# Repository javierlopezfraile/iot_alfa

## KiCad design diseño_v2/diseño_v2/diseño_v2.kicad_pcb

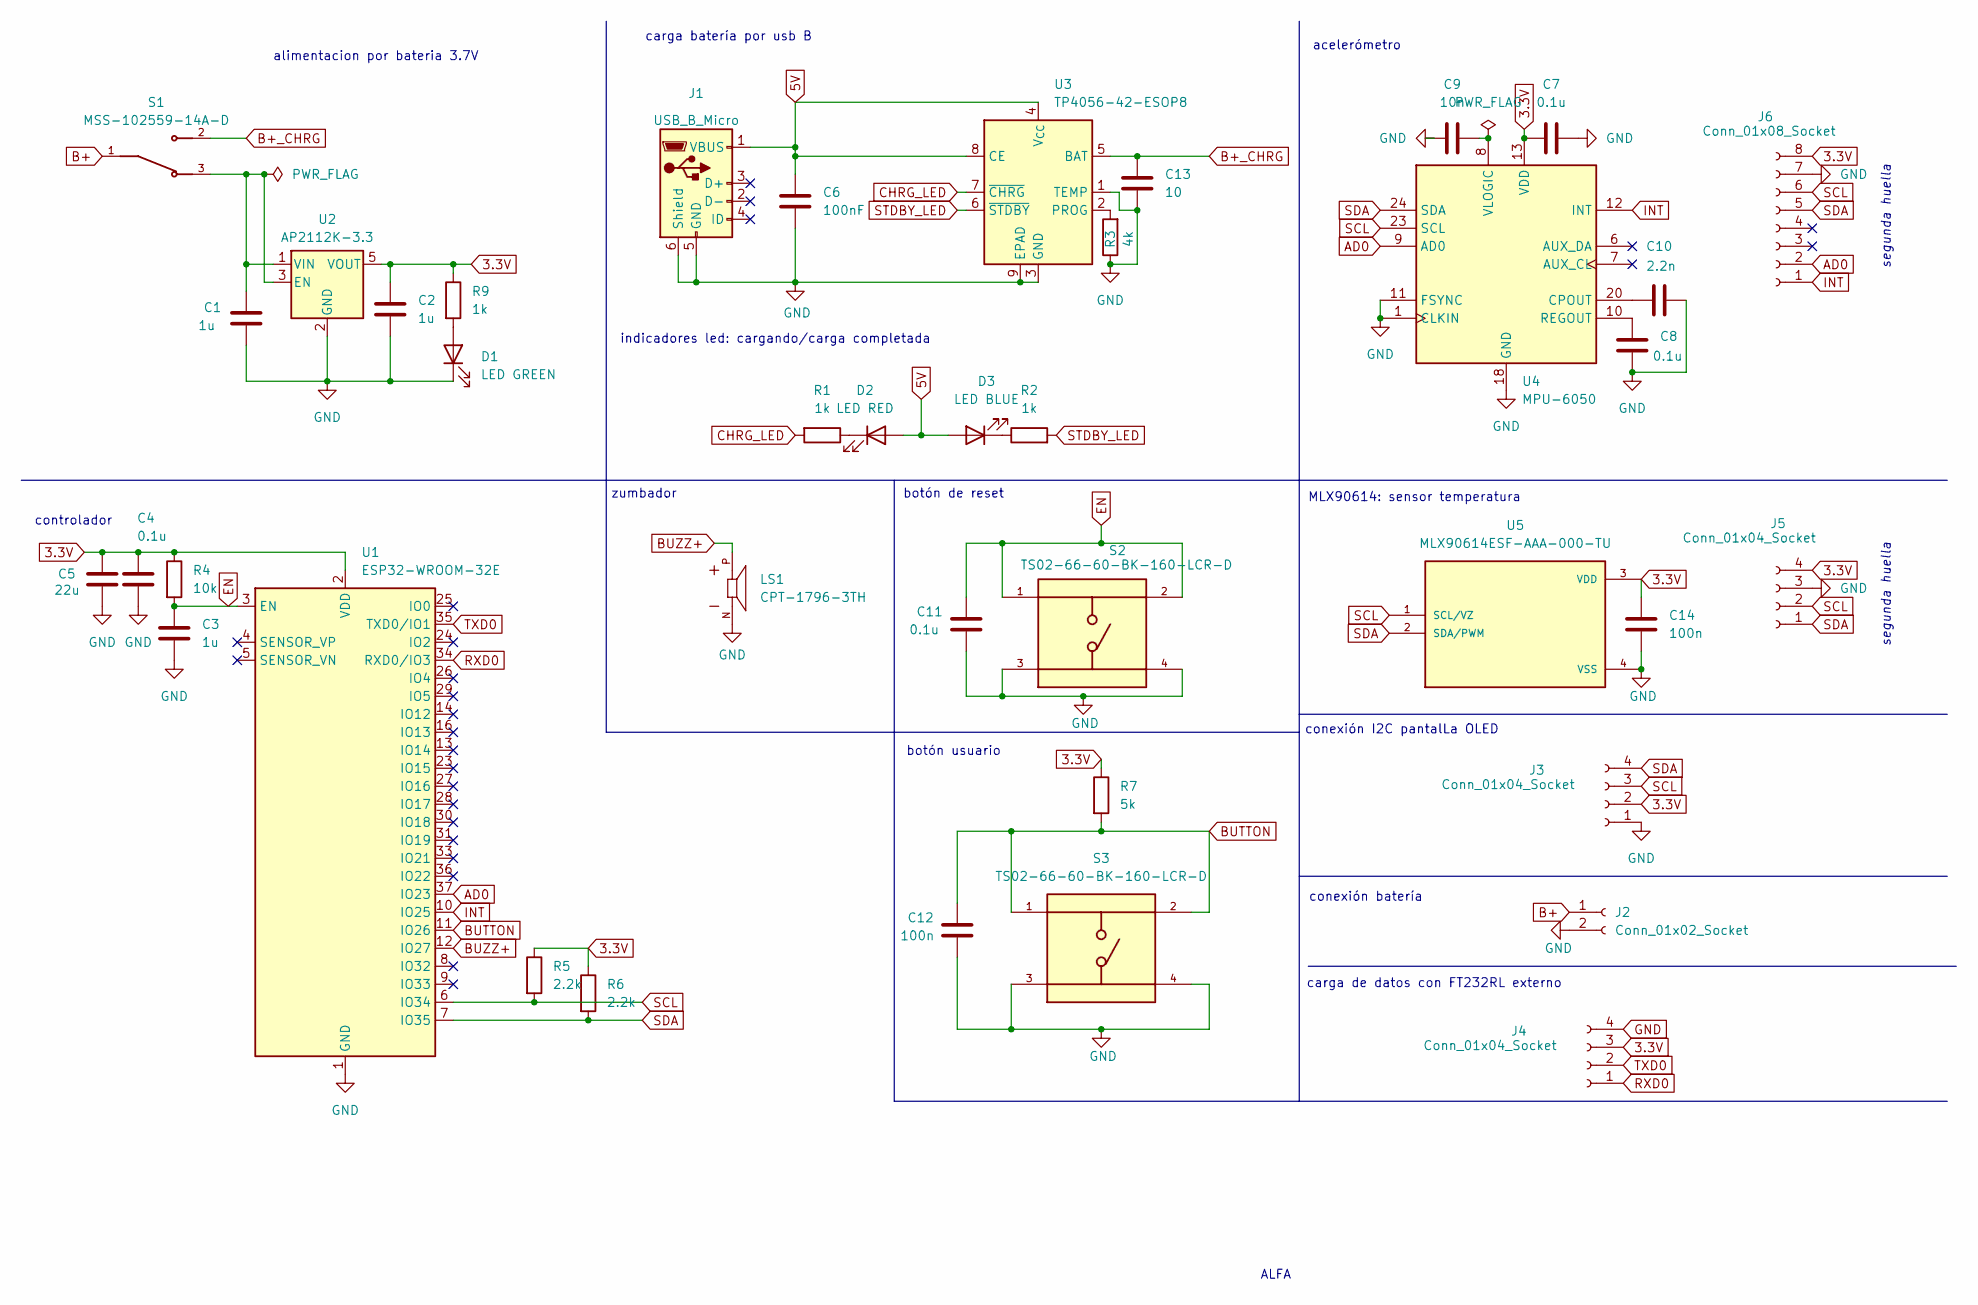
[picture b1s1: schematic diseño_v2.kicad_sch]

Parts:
C1, C2, C3: 1u; C_0805_2012Metric
C4, C7, C8, C11: 0.1u; C_0805_2012Metric
C5: 22u; C_0805_2012Metric
C6: 100nF; C_0805_2012Metric
C9: 10n; C_0805_2012Metric
C10: 2.2n; C_0805_2012Metric
C12, C14: 100n; C_0805_2012Metric
C13: 10; C_0805_2012Metric
D1: LED GREEN; LED_D3.0mm
D2: LED RED; LED_D3.0mm
D3: LED BLUE; LED_D3.0mm
J1: USB_B_Micro; USB_Micro-B_XKB_U254-051T-4BH83-F1S
J2: Conn_01x02_Socket; JST_PH_S2B-PH-K_1x02_P2.00mm_Horizontal
J3, J4, J5: Conn_01x04_Socket; PinSocket_1x04_P2.54mm_Vertical
J6: Conn_01x08_Socket; PinSocket_1x08_P2.54mm_Vertical
LS1: CPT-1796-3TH; SPKR_CPT-1796-3TH; PARTREV 1.0
R1, R2, R9: 1k; R_0805_2012Metric
R3: 4k; R_0805_2012Metric
R4: 10k; R_0805_2012Metric
R5, R6: 2.2k; R_0805_2012Metric
R7: 5k; R_0805_2012Metric
S1: MSS-102559-14A-D; SW_MSS-102559-14A-D; PARTREV 1.0
S2, S3: TS02-66-60-BK-160-LCR-D; SW_TS02-66-60-BK-160-LCR-D; PARTREV 1.0
U1: ESP32-WROOM-32E; ESP32-WROOM-32E-USER
U2: AP2112K-3.3; SOT-23-5
U3: TP4056-42-ESOP8; SOIC-8-1EP_3.9x4.9mm_P1.27mm_EP2.41x3.3mm_ThermalVias
U4: MPU-6050; InvenSense_QFN-24_4x4mm_P0.5mm
U5: MLX90614ESF-AAA-000-TU; TO254P912H435-4; PARTREV 13

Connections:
3.3V: C2.1, C4.1, C5.1, C7.1, C14.1, J3.2, J4.3, J5.4, J6.8, R4.1, R5.1, R6.1, R7.1, R9.1, U1.2 (VDD), U2.5 (VOUT), U4.13 (VDD), U5.3 (VDD)
5V: C6.1, D2.2 (A), D3.2 (A), J1.1 (VBUS), U3.4 (V_{CC}), U3.8 (CE)
AD0: J6.2, U1.37 (IO23), U4.9 (AD0)
B+: J2.1, S1.1
B+_CHRG: C13.1, S1.2, U3.5 (BAT)
BUTTON: C12.1, R7.2, S3.1, S3.2, U1.11 (IO26)
BUZZ+: LS1.P, U1.12 (IO27)
CHRG_LED: R1.2, U3.7 (~CHRG)
EN: C3.1, C11.1, R4.2, S2.1, S2.2, U1.3 (EN)
GND: C1.2, C2.2, C3.2, C4.2, C5.2, C6.2, C7.2, C8.2, C9.2, C10.2, C11.2, C12.2, C13.2, C14.2, D1.1 (K), J1.5 (GND), J1.6 (Shield), J2.2, J3.1, J4.4, J5.3, J6.7, LS1.N, R3.1, S2.3, S2.4, S3.3, S3.4, U1.1 (GND), U1.15 (GND), U1.38 (GND), U1.39 (GND), U2.2 (GND), U3.1 (TEMP), U3.3 (GND), U3.9 (EPAD), U4.1 (CLKIN), U4.11 (FSYNC), U4.18 (GND), U5.4 (VSS)
INT: J6.1, U1.10 (IO25), U4.12 (INT)
unnamed: D1.2 (A), R9.2
unnamed: D2.1 (K), R1.1
unnamed: D3.1 (K), R2.1
unnamed: C1.1, S1.3, U2.1 (VIN), U2.3 (EN)
unnamed: R3.2, U3.2 (PROG)
unnamed: C10.1, U4.20 (CPOUT)
unnamed: C8.1, U4.10 (REGOUT)
unnamed: C9.1, U4.8 (VLOGIC)
RXD0: J4.1, U1.34 (RXD0/IO3)
SCL: J3.3, J5.2, J6.6, R5.2, U1.6 (IO34), U4.23 (SCL), U5.1 (SCL/VZ)
SDA: J3.4, J5.1, J6.5, R6.2, U1.7 (IO35), U4.24 (SDA), U5.2 (SDA/PWM)
STDBY_LED: R2.2, U3.6 (~STDBY)
TXD0: J4.2, U1.35 (TXD0/IO1)

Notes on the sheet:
carga de datos con FT232RL externo
botón de reset
segunda huella
acelerómetro
alimentacion por bateria 3.7V
conexión I2C pantalLa OLED
zumbador
controlador
conexión batería
indicadores led: cargando/carga completada
carga batería por usb B
MLX90614: sensor temperatura
botón usuario
ALFA

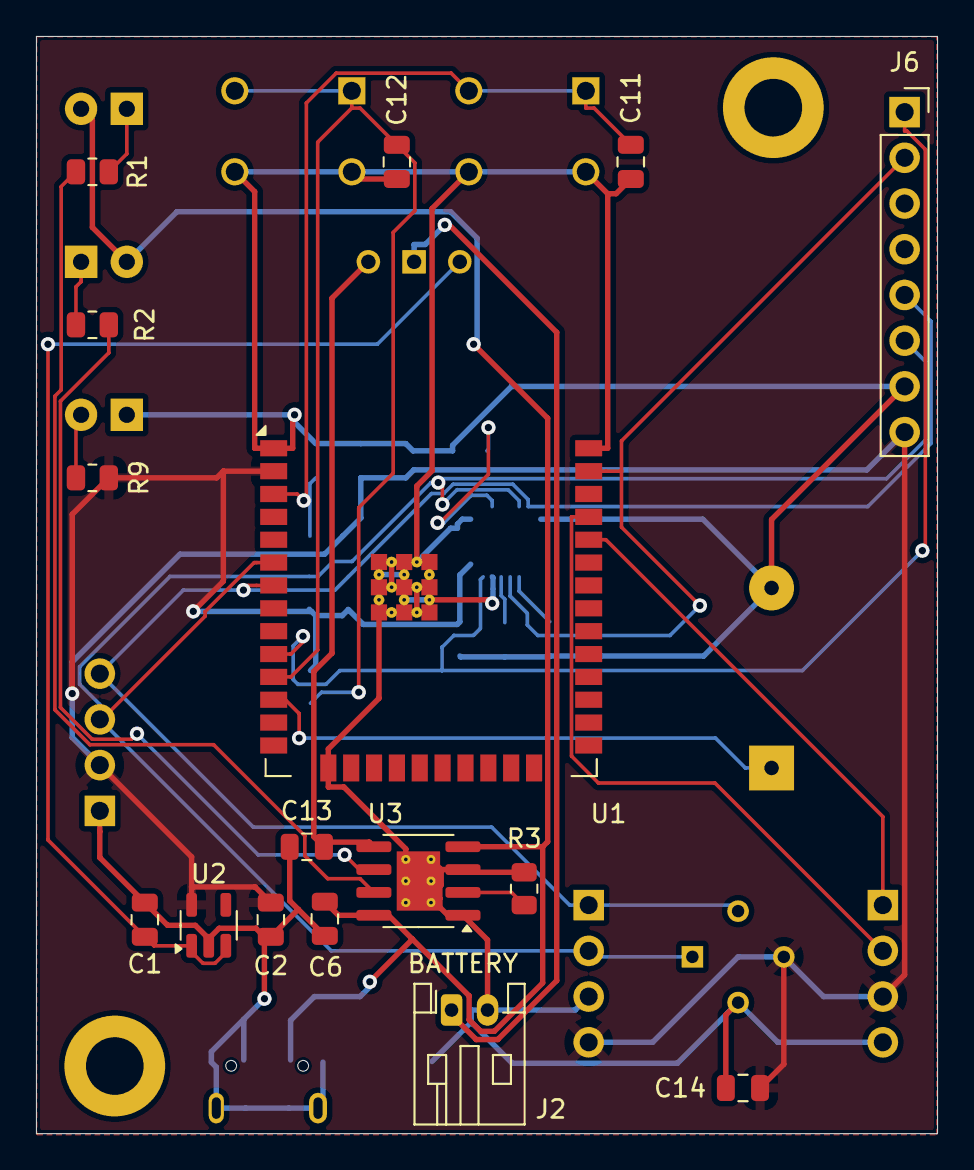
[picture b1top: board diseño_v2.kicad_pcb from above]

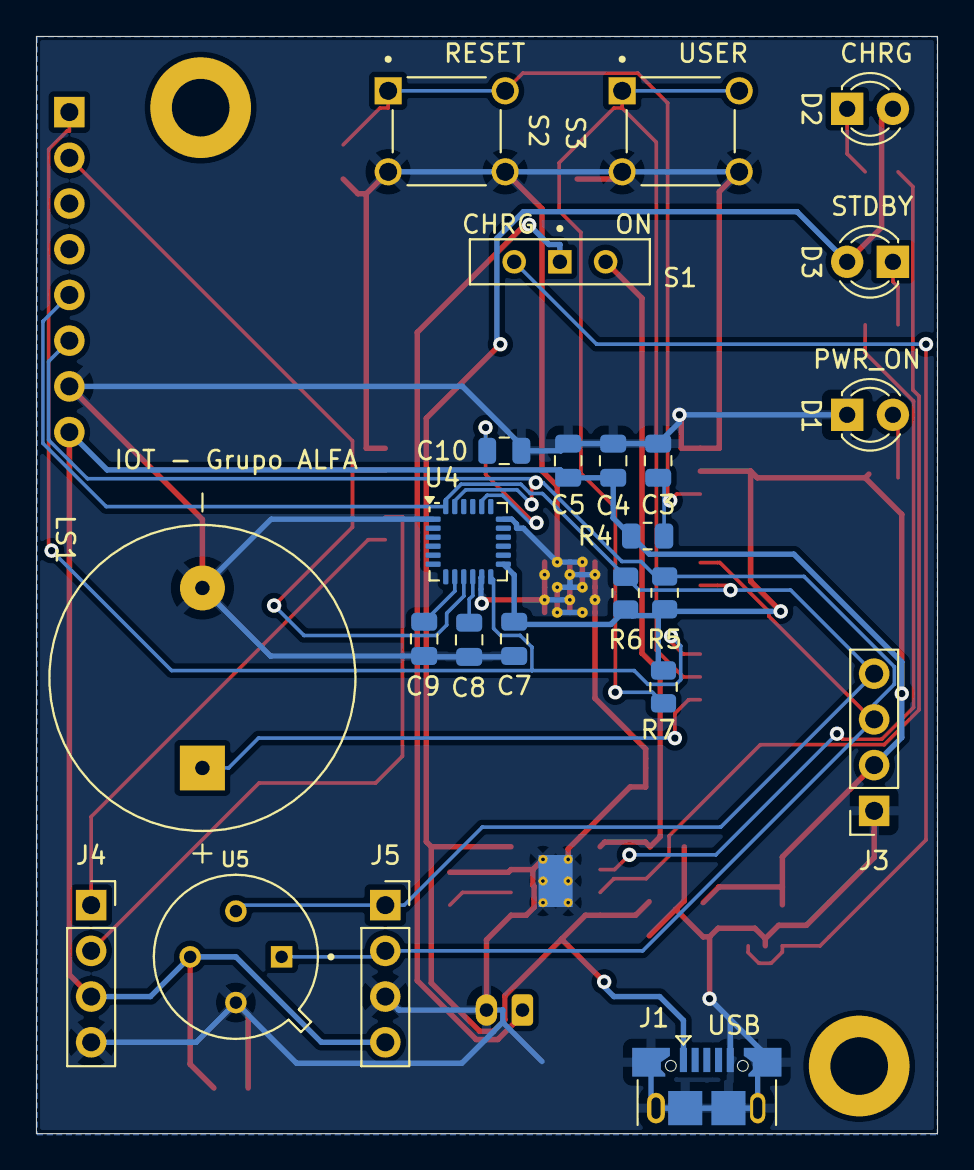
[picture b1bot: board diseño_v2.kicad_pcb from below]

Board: 2 copper layers, 50.1 x 61.0 mm, 40 parts (24 on the bottom side), 24 nets.

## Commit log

2025-11-06 Create n
2025-11-08 Primera versión de la clase PantallaOLED
    Contiene distintas funciones para inicializar, encender, apagar y mostrar datos en la pantalla OLED SSD1306
2025-11-08 Create pantalla.ino version 0.1
    Versión a mitad de desarrollo de la clase PantallaOLED que se encarga de toda la configuración y utilidades de nuestra pantalla oled
2025-11-12 Primer versión de la web. Sólo para probar las funcionalidades.
2025-11-12 Primer versión del código del web.
2025-11-13 Create mlx90614_v1.ino
    Primera versión funcional del sensor de temperatura
2025-11-13 avanzaodo con el proceso de actualización de datos en la web
2025-11-13 minor debuging.
2025-11-13 Avanzado con el proceso de la actualización de los datos en la página web.
2025-11-20 Acelerómetro v1
2025-11-20 Move web code to codigo_web directory and fix typos.
2025-11-21 acelerómetro v2 sin utilizar delay
2025-11-25 Sensor temperatura mejorado incluyendo gestión del botón
2025-11-27 Pantalla v2 -> Más funciones para distintas respuestas
2025-11-27 Mejorado las funciones sobre la json y la iteración de datos en las formas.
2025-11-27 Hecho comentario la frase de escribir por serial de json para probación de su funcionamieto.
2025-11-27 Los 3 sensores funcionando a la vez
    Se mejora la lógica de botones para que funcionen a la vez y se añade algún método en la clase de temperatura.
2025-11-27 diseño final PCB
2025-11-29 Add files via upload
    Se ha añadido la funcion de conectarse al wifi y que lea el dia y la hora de un servidor ntp
2025-11-29 Hora funcionando online y offline
2025-11-29 hecha página web con texto de prueba
2025-11-29 Página web con medidas reales
2025-11-29 web.h de codigo_web con algunas modificaciones
2025-12-09 Código de prueba del buzzer para la PCB
2025-12-10 Mejoras en la visualización de la pantalla
2025-12-10 Arreglo bug de pantalla que no se apaga en displayEnhorabuena
2025-12-10 Nuevo método displayBienvenida
2025-12-10 Nuevos métodos para ver en el display la conexión y desconexión a internet
2025-12-11 Actualización segundos al visualizar la hora en el display
2025-12-15 Gestión básica memoria
2025-12-16 Parsear con la librería ArduinoJson los datos cargados de la memoria
2025-12-17 Gestión bajo consumo ESP32
2025-12-17 Despertar por movimiento + Buzzer
2025-12-18 Corrección bug acelerómetro
2025-12-18 Mejora lógica para entrar en deep sleep
2025-12-18 Corrección bug memoria
2025-12-18 Otra corrección memoria
2025-12-18 Corrección umbrales temperatura
2025-12-19 últimas mejoras
